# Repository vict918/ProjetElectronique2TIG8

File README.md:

# Projet d’électronique 2TL2

Groupe :
- Castermane Robin
- Cotton Victor
- Mugisha Rodrigue
- Vandervelden Igor

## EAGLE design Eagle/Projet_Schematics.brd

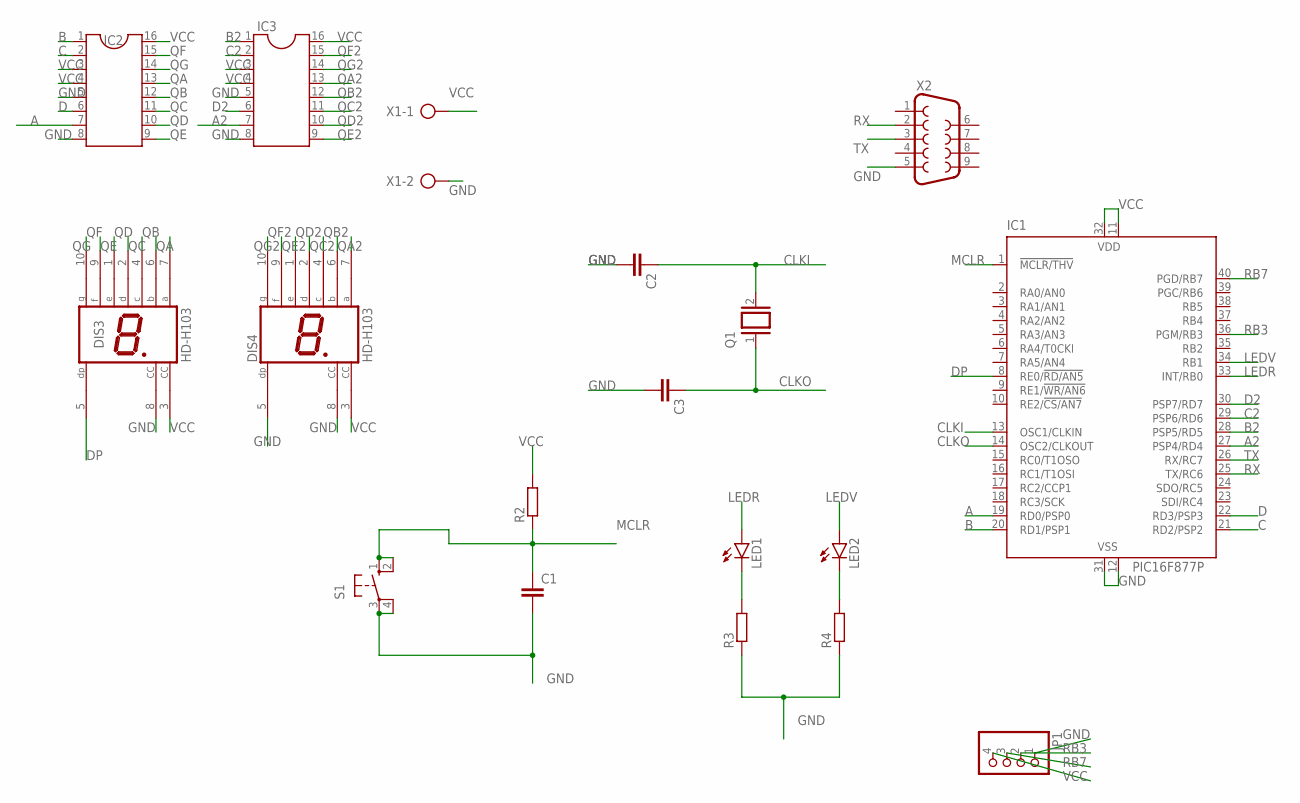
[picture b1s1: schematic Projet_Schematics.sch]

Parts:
C1, C2, C3: C-EU025-030X050; C025-030X050
DIS3, DIS4: HD-H103; HDSP-M
IC1: PIC16F877P; DIL40
IC2, IC3: DIL16
JP1: PINHD-1X4; 1X04
LED1, LED2: LED5MM
Q1: XTAL/S; QS
R2, R3, R4: R-EU_0204/7; 0204/7
S1: 10-XX; B3F-10XX
X1: AK300/2
X2: F09H

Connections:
A: IC1.19 (RD0/PSP0), IC2.7
A2: IC1.27 (PSP4/RD4), IC3.7
B: IC1.20 (RD1/PSP1), IC2.1
B2: IC1.28 (PSP5/RD5), IC3.1
C: IC1.21 (RD2/PSP2), IC2.2
C2: IC1.29 (PSP6/RD6), IC3.2
CLKI: C2.1, IC1.13 (OSC1/CLKIN), Q1.2
CLKO: C3.1, IC1.14 (OSC2/CLKOUT), Q1.1
D: IC1.22 (RD3/PSP3), IC2.6
D2: IC1.30 (PSP7/RD7), IC3.6
DP: DIS3.5 (DP), IC1.8 (RE0/!RD/AN5)
GND: C1.2, C2.2, C3.2, DIS3.8 (CC), DIS4.5 (DP), DIS4.8 (CC), IC1.12 (VSS), IC1.31 (VSS), IC2.5, IC2.8, IC3.5, IC3.8, JP1.1, R3.1, R4.1, S1.3, S1.4 (P1), X1.2, X2.5
LEDR: IC1.33 (INT/RB0), LED1.A
LEDV: IC1.34 (RB1), LED2.A
MCLR: C1.1, IC1.1 (!MCLR/THV), R2.1, S1.1 (S), S1.2 (S1)
unnamed: LED1.K (C), R3.2
unnamed: LED2.K (C), R4.2
QA: DIS3.7 (A), IC2.13
QA2: DIS4.7 (A), IC3.13
QB: DIS3.6 (B), IC2.12
QB2: DIS4.6 (B), IC3.12
QC: DIS3.4 (C), IC2.11
QC2: DIS4.4 (C), IC3.11
QD: DIS3.2 (D), IC2.10
QD2: DIS4.2 (D), IC3.10
QE: DIS3.1 (E), IC2.9
QE2: DIS4.1 (E), IC3.9
QF: DIS3.9 (F), IC2.15
QF2: DIS4.9 (F), IC3.15
QG: DIS3.10 (G), IC2.14
QG2: DIS4.10 (G), IC3.14
RB3: IC1.36 (PGM/RB3), JP1.2
RB7: IC1.40 (PGD/RB7), JP1.3
RX: IC1.25 (TX/RC6), X2.2
TX: IC1.26 (RX/RC7), X2.3
VCC: DIS3.3 (CC), DIS4.3 (CC), IC1.11 (VDD), IC1.32 (VDD), IC2.3, IC2.4, IC2.16, IC3.3, IC3.4, IC3.16, JP1.4, R2.2, X1.1

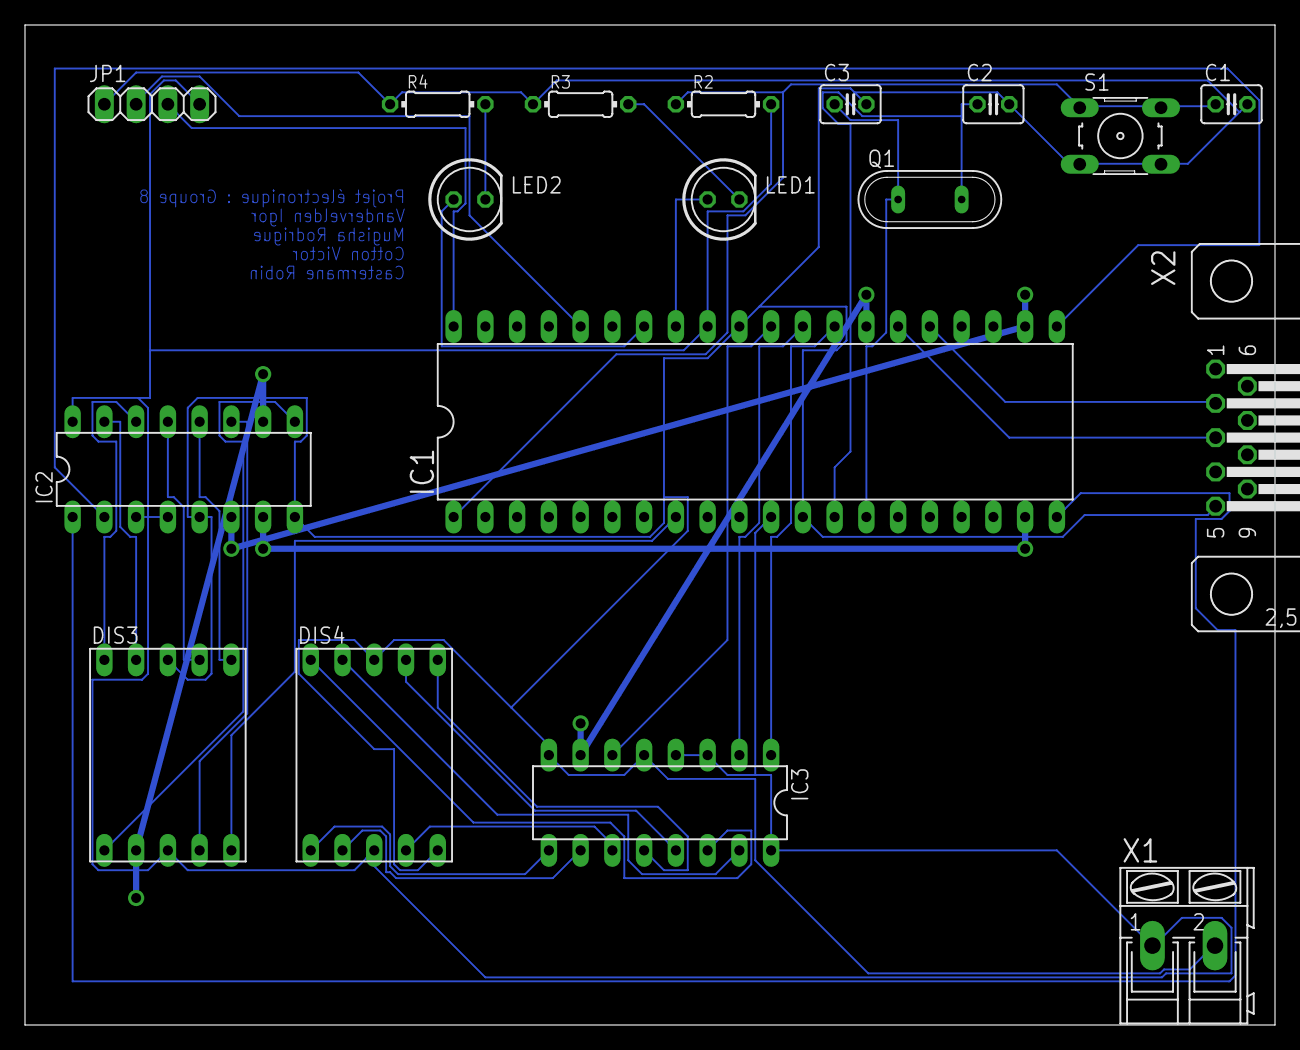
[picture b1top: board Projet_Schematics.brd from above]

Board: 2 copper layers, 100.0 x 80.0 mm, 18 parts (0 on the bottom side), 36 nets.

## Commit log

2020-03-05 test
2020-03-05 schéma proteus
2020-03-05 Schéma update + test code C
2020-03-09 Structure Git
2020-03-09 Board Eagle
2020-03-09 Révision board
2020-03-09 brd final
2020-03-09 Maj rapport, eagle, codeC
2020-03-09 Correction orthographe
2020-03-09 Rename fichier
2020-04-29 update code C
2020-04-29 Début implementation application Java
2020-04-30 schéma proteus final
2020-04-30 Code c Update
2020-05-05 Modif C
2020-05-05 Code C Modif
2020-05-05 Code C Finalisation
2020-05-09 Application Java fonctionelle
2020-05-09 Renommage dossier Java
2020-05-09 Update java
2020-05-09 Ajouts commentaires
2020-05-09 Code C Final
2020-05-10 Code C dernière modif
2020-05-10 Finalisation appli Java
2020-05-10 Modifs finales appli. java
2020-05-11 Suppression dossier
